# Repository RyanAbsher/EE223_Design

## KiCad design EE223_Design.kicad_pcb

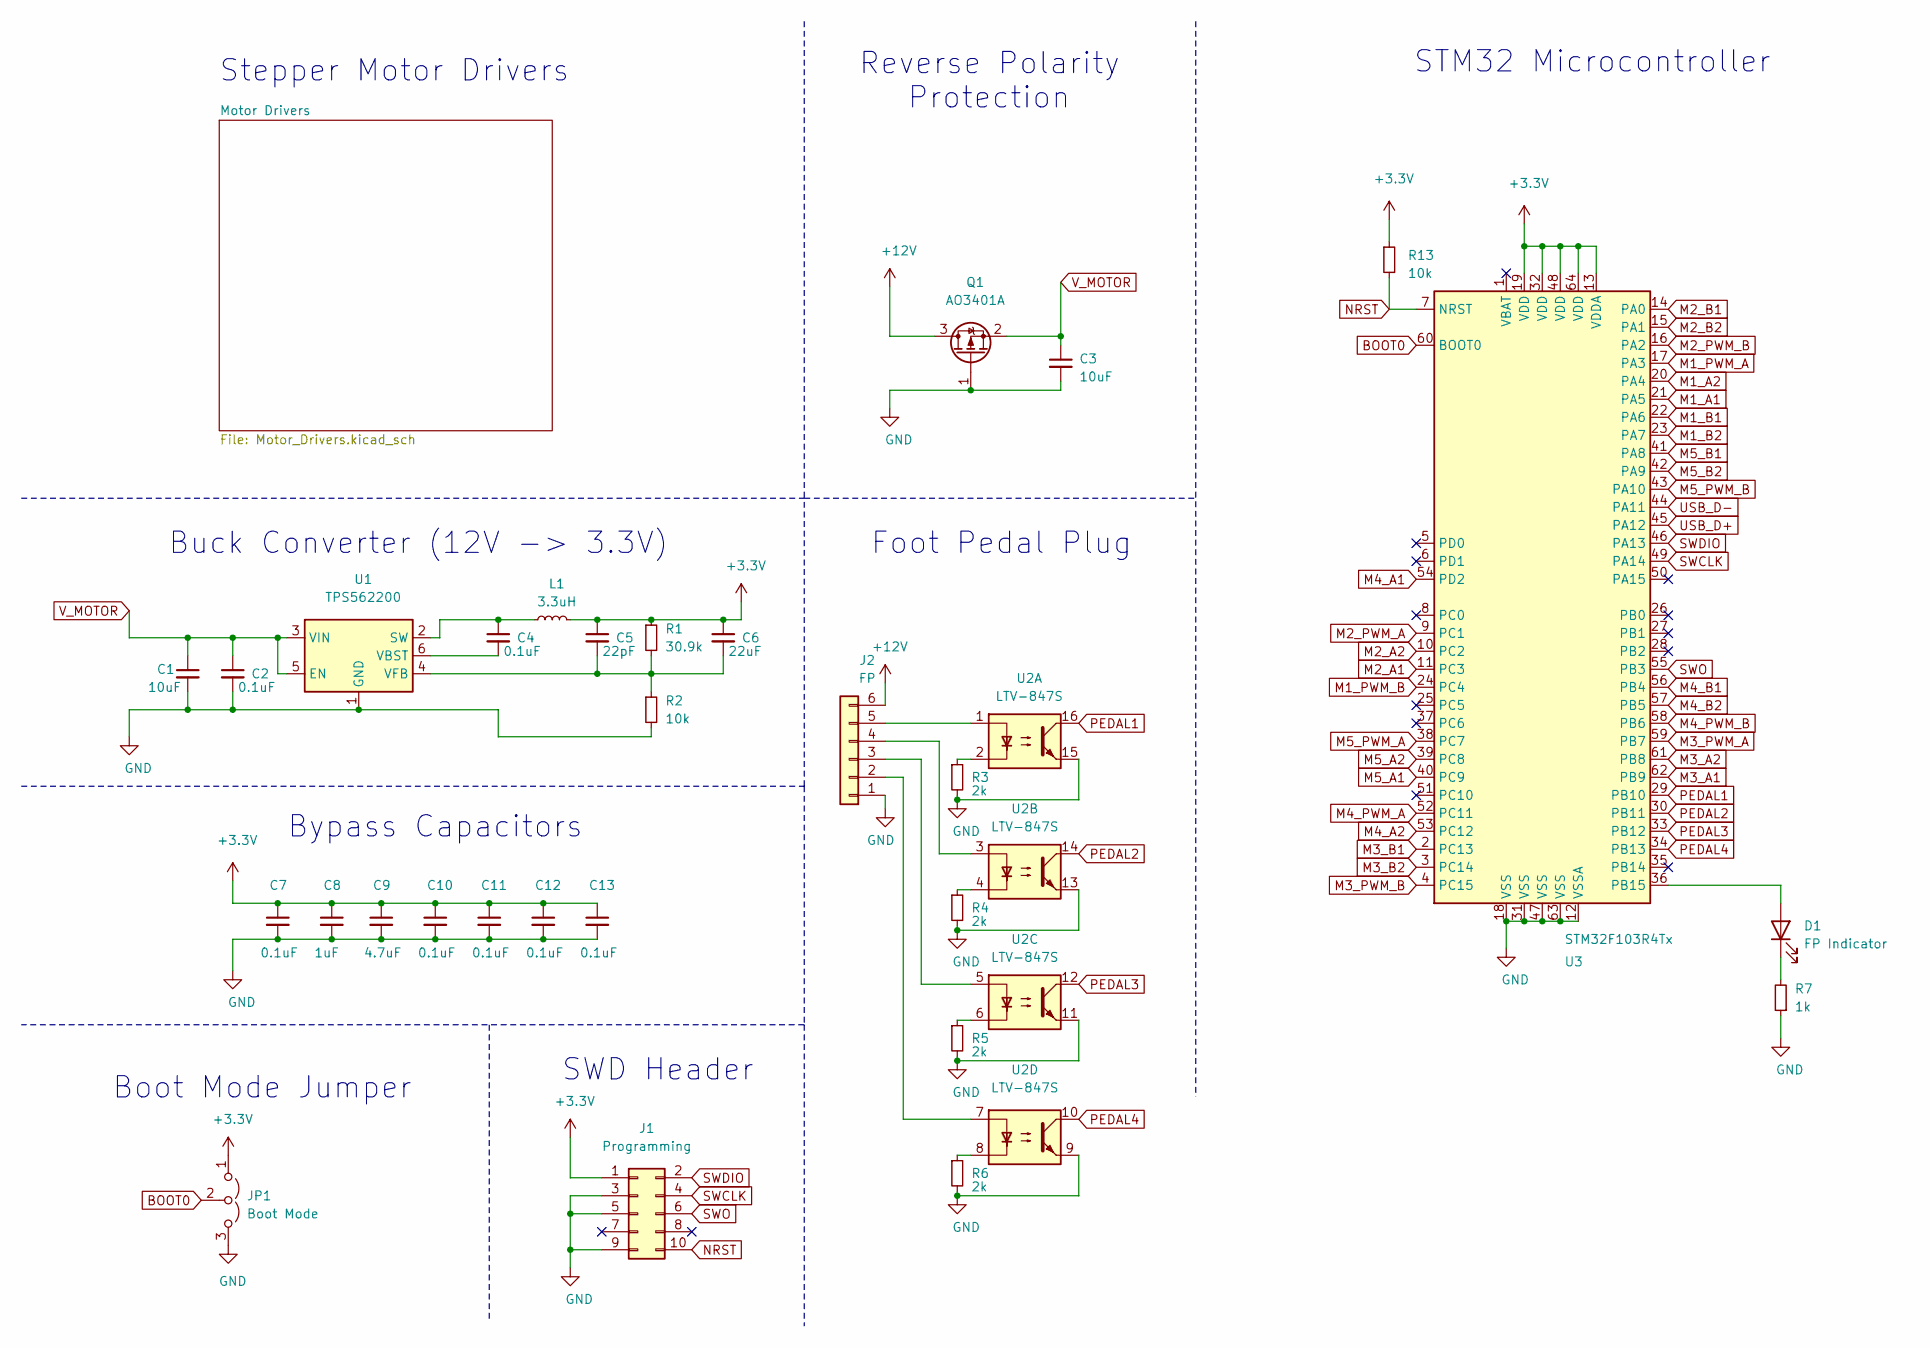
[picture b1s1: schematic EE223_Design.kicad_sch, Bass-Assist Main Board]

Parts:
C1, C3: 10uF; C_0402_1005Metric_Pad0.74x0.62mm_HandSolder
C2, C4, C7, C10, C11, C12, C13: 0.1uF; C_0402_1005Metric_Pad0.74x0.62mm_HandSolder
C5: 22pF; C_0402_1005Metric_Pad0.74x0.62mm_HandSolder
C6: 22uF; C_0402_1005Metric_Pad0.74x0.62mm_HandSolder
C8: 1uF; C_0402_1005Metric_Pad0.74x0.62mm_HandSolder
C9: 4.7uF; C_0402_1005Metric_Pad0.74x0.62mm_HandSolder
D1: FP Indicator; LED_D5.0mm
J1: Programming; PinHeader_2x05_P1.27mm_Vertical
J2: FP; Molex_KK-254_AE-6410-06A_1x06_P2.54mm_Vertical
JP1: Boot Mode; PinHeader_1x03_P2.54mm_Vertical
L1: 3.3uH; VLS6045AF
Q1: AO3401A; SOT-23
R1: 30.9k; R_0402_1005Metric_Pad0.72x0.64mm_HandSolder
R2, R13: 10k; R_0402_1005Metric_Pad0.72x0.64mm_HandSolder
R3, R4, R5, R6: 2k; R_0402_1005Metric_Pad0.72x0.64mm_HandSolder
R7: 1k; R_0402_1005Metric_Pad0.72x0.64mm_HandSolder
U1: TPS562200; SOT-23-6
U2: LTV-847S; SMDIP-16_W9.53mm
U3: STM32F103R4Tx; LQFP-64_10x10mm_P0.5mm

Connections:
+3V3: C5.1, C6.1, C7.1, C8.1, C9.1, C10.1, C11.1, C12.1, C13.1, J1.1, JP1.1 (A), L1.2, R1.1, R13.1, U3.13 (VDDA), U3.19 (VDD), U3.32 (VDD), U3.48 (VDD), U3.64 (VDD); also elsewhere on the board
+12V: J2.6, Q1.3 (D)
BOOT0: JP1.2 (C), U3.60 (BOOT0)
GND: C1.2, C2.2, C3.2, C7.2, C8.2, C9.2, C10.2, C11.2, C12.2, C13.2, J1.3, J1.5, J1.9, J2.1, JP1.3 (B), Q1.1 (G), R2.2, R3.2, R4.2, R5.2, R6.2, R7.1, U1.1 (GND), U2.9, U2.11, U2.13, U2.15, U3.12 (VSSA), U3.18 (VSS), U3.31 (VSS), U3.47 (VSS), U3.63 (VSS); also elsewhere on the board
M1_A1: U3.21 (PA5); also elsewhere on the board
M1_A2: U3.20 (PA4); also elsewhere on the board
M1_B1: U3.22 (PA6); also elsewhere on the board
M1_B2: U3.23 (PA7); also elsewhere on the board
M1_PWM_A: U3.17 (PA3); also elsewhere on the board
M1_PWM_B: U3.24 (PC4); also elsewhere on the board
M2_A1: U3.11 (PC3); also elsewhere on the board
M2_A2: U3.10 (PC2); also elsewhere on the board
M2_B1: U3.14 (PA0); also elsewhere on the board
M2_B2: U3.15 (PA1); also elsewhere on the board
M2_PWM_A: U3.9 (PC1); also elsewhere on the board
M2_PWM_B: U3.16 (PA2); also elsewhere on the board
M3_A1: U3.62 (PB9); also elsewhere on the board
M3_A2: U3.61 (PB8); also elsewhere on the board
M3_B1: U3.2 (PC13); also elsewhere on the board
M3_B2: U3.3 (PC14); also elsewhere on the board
M3_PWM_A: U3.59 (PB7); also elsewhere on the board
M3_PWM_B: U3.4 (PC15); also elsewhere on the board
M4_A1: U3.54 (PD2); also elsewhere on the board
M4_A2: U3.53 (PC12); also elsewhere on the board
M4_B1: U3.56 (PB4); also elsewhere on the board
M4_B2: U3.57 (PB5); also elsewhere on the board
M4_PWM_A: U3.52 (PC11); also elsewhere on the board
M4_PWM_B: U3.58 (PB6); also elsewhere on the board
M5_A1: U3.40 (PC9); also elsewhere on the board
M5_A2: U3.39 (PC8); also elsewhere on the board
M5_B1: U3.41 (PA8); also elsewhere on the board
M5_B2: U3.42 (PA9); also elsewhere on the board
M5_PWM_A: U3.38 (PC7); also elsewhere on the board
M5_PWM_B: U3.43 (PA10); also elsewhere on the board
NRST: J1.10, R13.2, U3.7 (NRST)
unnamed: C4.1, L1.1, U1.2 (SW)
unnamed: C4.2, U1.6 (VBST)
unnamed: C5.2, C6.2, R1.2, R2.1, U1.4 (VFB)
unnamed: D1.1 (K), R7.2
unnamed: D1.2 (A), U3.36 (PB15)
unnamed: J2.2, U2.7
unnamed: J2.3, U2.5
unnamed: J2.4, U2.3
unnamed: J2.5, U2.1
unnamed: R3.1, U2.2
unnamed: R4.1, U2.4
unnamed: R5.1, U2.6
unnamed: R6.1, U2.8
PEDAL1: U2.16, U3.29 (PB10)
PEDAL2: U2.14, U3.30 (PB11)
PEDAL3: U2.12, U3.33 (PB12)
PEDAL4: U2.10, U3.34 (PB13)
SWCLK: J1.4, U3.49 (PA14)
SWDIO: J1.2, U3.46 (PA13)
SWO: J1.6, U3.55 (PB3)
USB_D+: U3.45 (PA12)
USB_D-: U3.44 (PA11)
V_MOTOR: C1.1, C2.1, C3.1, Q1.2 (S), U1.3 (VIN), U1.5 (EN); also elsewhere on the board

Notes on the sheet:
Boot Mode Jumper
Stepper Motor Drivers
Bypass Capacitors
Buck Converter (12V -> 3.3V)
SWD Header
Reverse Polarity Protection
Foot Pedal Plug
STM32 Microcontroller

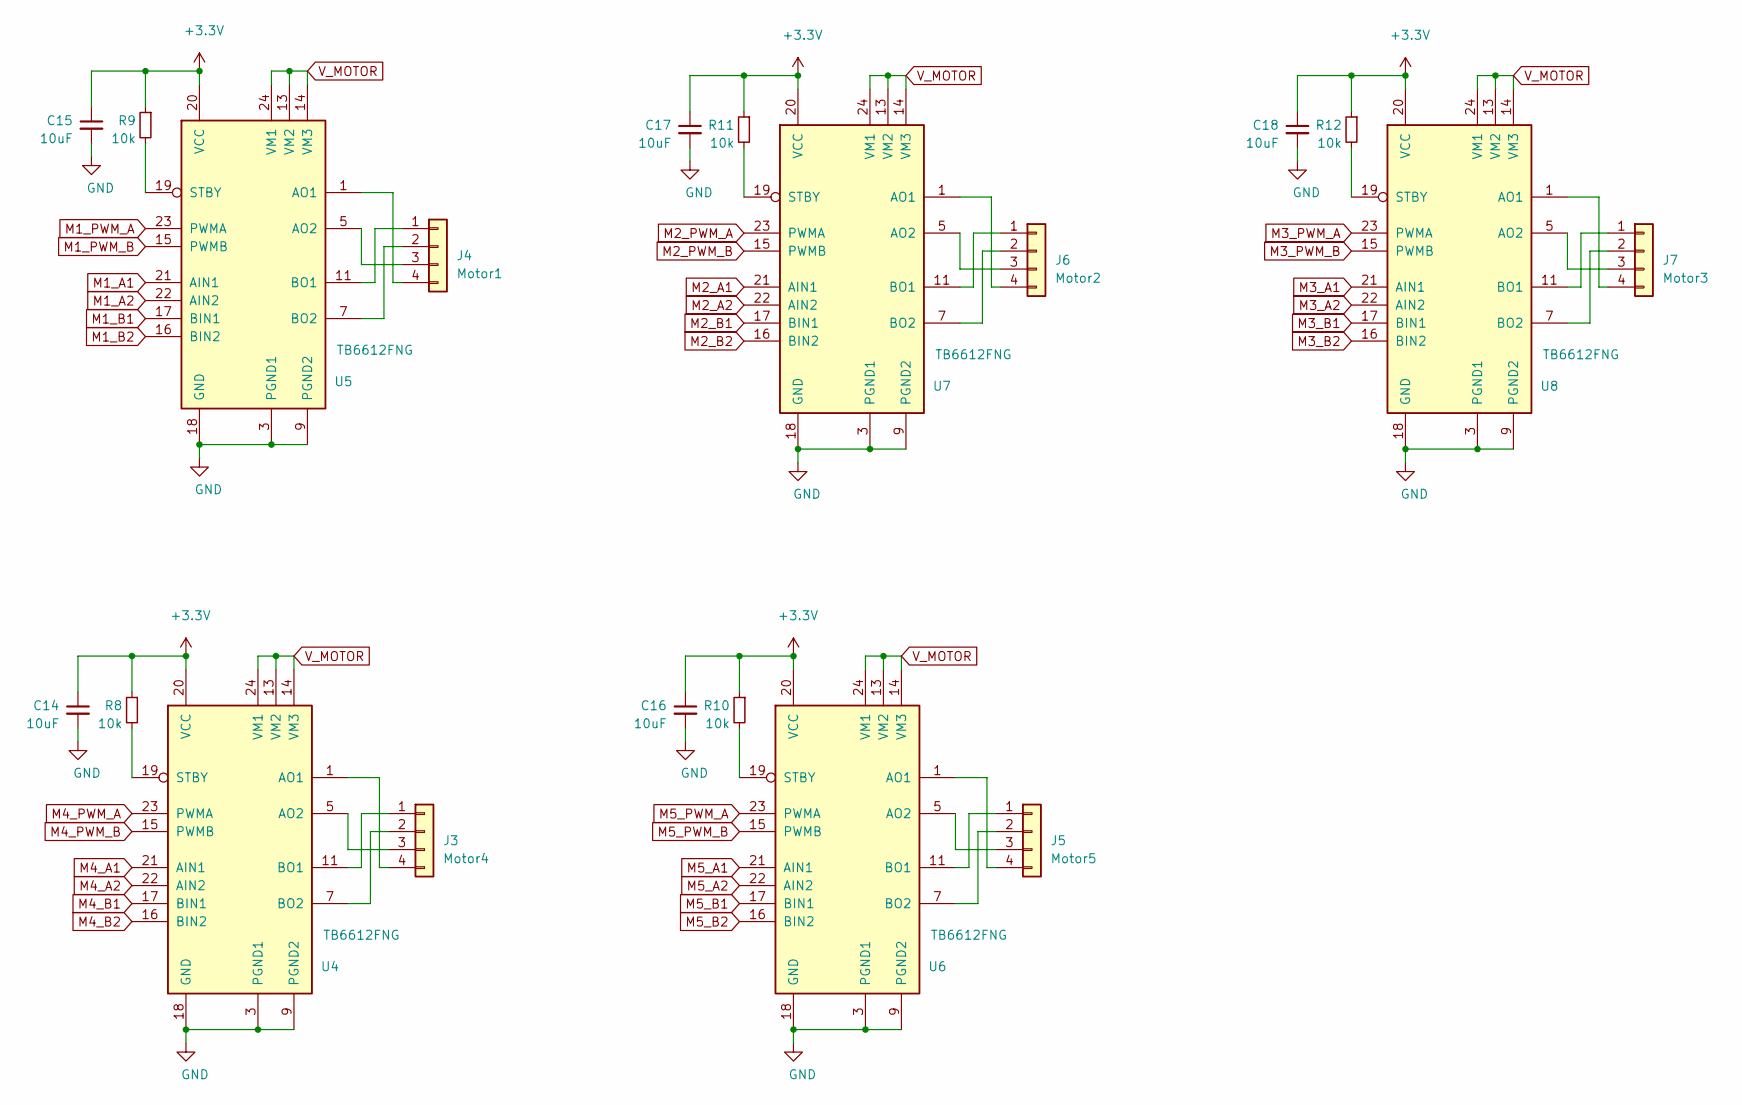
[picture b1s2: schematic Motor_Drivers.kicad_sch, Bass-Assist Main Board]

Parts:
C14, C15, C16, C17, C18: 10uF; C_0402_1005Metric_Pad0.74x0.62mm_HandSolder
J3: Motor4; Molex_KK-254_AE-6410-04A_1x04_P2.54mm_Vertical
J4: Motor1; Molex_KK-254_AE-6410-04A_1x04_P2.54mm_Vertical
J5: Motor5; Molex_KK-254_AE-6410-04A_1x04_P2.54mm_Vertical
J6: Motor2; Molex_KK-254_AE-6410-04A_1x04_P2.54mm_Vertical
J7: Motor3; Molex_KK-254_AE-6410-04A_1x04_P2.54mm_Vertical
R8, R9, R10, R11, R12: 10k; R_0402_1005Metric_Pad0.72x0.64mm_HandSolder
U4, U5, U6, U7, U8: TB6612FNG; SSOP-24_5.3x8.2mm_P0.65mm

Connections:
+3V3: C14.1, C15.1, C16.1, C17.1, C18.1, R8.1, R9.1, R10.1, R11.1, R12.1, U4.20 (VCC), U5.20 (VCC), U6.20 (VCC), U7.20 (VCC), U8.20 (VCC); also elsewhere on the board
GND: C14.2, C15.2, C16.2, C17.2, C18.2, U4.3 (PGND1), U4.4 (PGND1), U4.9 (PGND2), U4.10 (PGND2), U4.18 (GND), U5.3 (PGND1), U5.4 (PGND1), U5.9 (PGND2), U5.10 (PGND2), U5.18 (GND), U6.3 (PGND1), U6.4 (PGND1), U6.9 (PGND2), U6.10 (PGND2), U6.18 (GND), U7.3 (PGND1), U7.4 (PGND1), U7.9 (PGND2), U7.10 (PGND2), U7.18 (GND), U8.3 (PGND1), U8.4 (PGND1), U8.9 (PGND2), U8.10 (PGND2), U8.18 (GND); also elsewhere on the board
M1_A1: U5.21 (AIN1); also elsewhere on the board
M1_A2: U5.22 (AIN2); also elsewhere on the board
M1_B1: U5.17 (BIN1); also elsewhere on the board
M1_B2: U5.16 (BIN2); also elsewhere on the board
M1_PWM_A: U5.23 (PWMA); also elsewhere on the board
M1_PWM_B: U5.15 (PWMB); also elsewhere on the board
M2_A1: U7.21 (AIN1); also elsewhere on the board
M2_A2: U7.22 (AIN2); also elsewhere on the board
M2_B1: U7.17 (BIN1); also elsewhere on the board
M2_B2: U7.16 (BIN2); also elsewhere on the board
M2_PWM_A: U7.23 (PWMA); also elsewhere on the board
M2_PWM_B: U7.15 (PWMB); also elsewhere on the board
M3_A1: U8.21 (AIN1); also elsewhere on the board
M3_A2: U8.22 (AIN2); also elsewhere on the board
M3_B1: U8.17 (BIN1); also elsewhere on the board
M3_B2: U8.16 (BIN2); also elsewhere on the board
M3_PWM_A: U8.23 (PWMA); also elsewhere on the board
M3_PWM_B: U8.15 (PWMB); also elsewhere on the board
M4_A1: U4.21 (AIN1); also elsewhere on the board
M4_A2: U4.22 (AIN2); also elsewhere on the board
M4_B1: U4.17 (BIN1); also elsewhere on the board
M4_B2: U4.16 (BIN2); also elsewhere on the board
M4_PWM_A: U4.23 (PWMA); also elsewhere on the board
M4_PWM_B: U4.15 (PWMB); also elsewhere on the board
M5_A1: U6.21 (AIN1); also elsewhere on the board
M5_A2: U6.22 (AIN2); also elsewhere on the board
M5_B1: U6.17 (BIN1); also elsewhere on the board
M5_B2: U6.16 (BIN2); also elsewhere on the board
M5_PWM_A: U6.23 (PWMA); also elsewhere on the board
M5_PWM_B: U6.15 (PWMB); also elsewhere on the board
unnamed: J3.1, U4.11 (BO1), U4.12 (BO1)
unnamed: J3.2, U4.7 (BO2), U4.8 (BO2)
unnamed: J3.3, U4.5 (AO2), U4.6 (AO2)
unnamed: J3.4, U4.1 (AO1), U4.2 (AO1)
unnamed: J5.1, U6.11 (BO1), U6.12 (BO1)
unnamed: J5.2, U6.7 (BO2), U6.8 (BO2)
unnamed: J5.3, U6.5 (AO2), U6.6 (AO2)
unnamed: J5.4, U6.1 (AO1), U6.2 (AO1)
unnamed: J6.1, U7.11 (BO1), U7.12 (BO1)
unnamed: J6.2, U7.7 (BO2), U7.8 (BO2)
unnamed: J6.3, U7.5 (AO2), U7.6 (AO2)
unnamed: J6.4, U7.1 (AO1), U7.2 (AO1)
unnamed: J7.1, U8.11 (BO1), U8.12 (BO1)
unnamed: J7.2, U8.7 (BO2), U8.8 (BO2)
unnamed: J7.3, U8.5 (AO2), U8.6 (AO2)
unnamed: J7.4, U8.1 (AO1), U8.2 (AO1)
unnamed: R8.2, U4.19 (STBY)
unnamed: R9.2, U5.19 (STBY)
unnamed: R10.2, U6.19 (STBY)
unnamed: R11.2, U7.19 (STBY)
unnamed: R12.2, U8.19 (STBY)
unnamed: J4.4, U5.1 (AO1), U5.2 (AO1)
unnamed: J4.3, U5.5 (AO2), U5.6 (AO2)
unnamed: J4.2, U5.7 (BO2), U5.8 (BO2)
unnamed: J4.1, U5.11 (BO1), U5.12 (BO1)
V_MOTOR: U4.13 (VM2), U4.14 (VM3), U4.24 (VM1), U5.13 (VM2), U5.14 (VM3), U5.24 (VM1), U6.13 (VM2), U6.14 (VM3), U6.24 (VM1), U7.13 (VM2), U7.14 (VM3), U7.24 (VM1), U8.13 (VM2), U8.14 (VM3), U8.24 (VM1); also elsewhere on the board

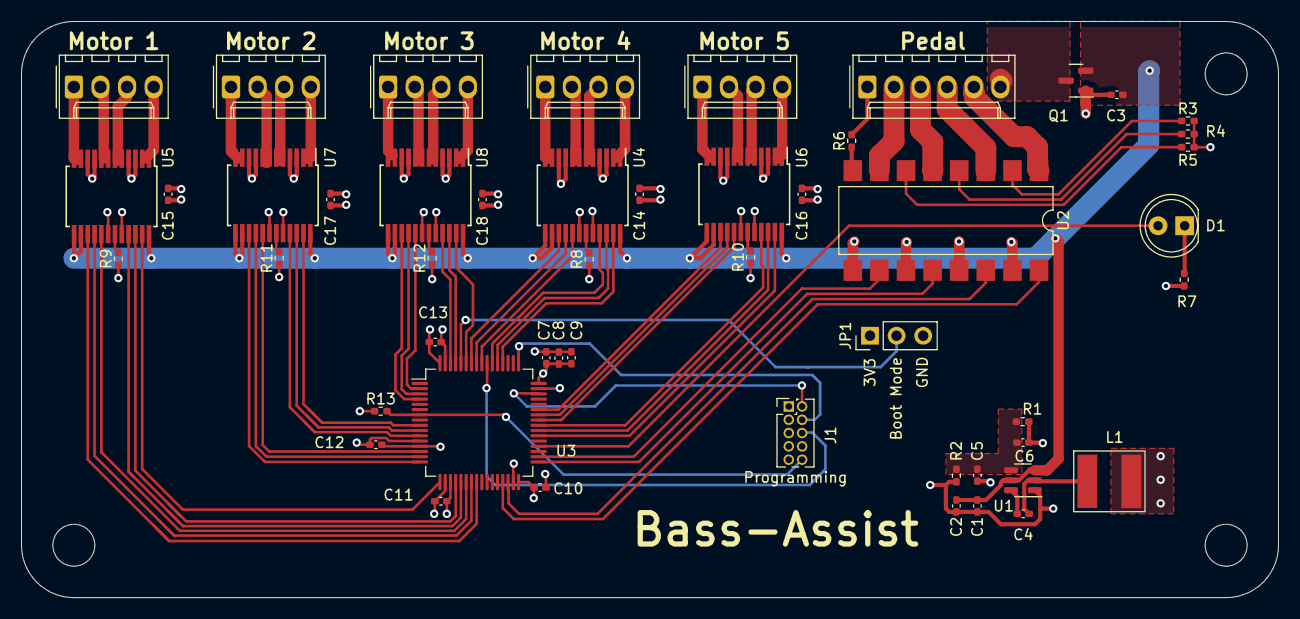
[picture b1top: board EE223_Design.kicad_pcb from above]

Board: 4 copper layers, 120.0 x 55.0 mm, 50 parts (0 on the bottom side), 81 nets.
